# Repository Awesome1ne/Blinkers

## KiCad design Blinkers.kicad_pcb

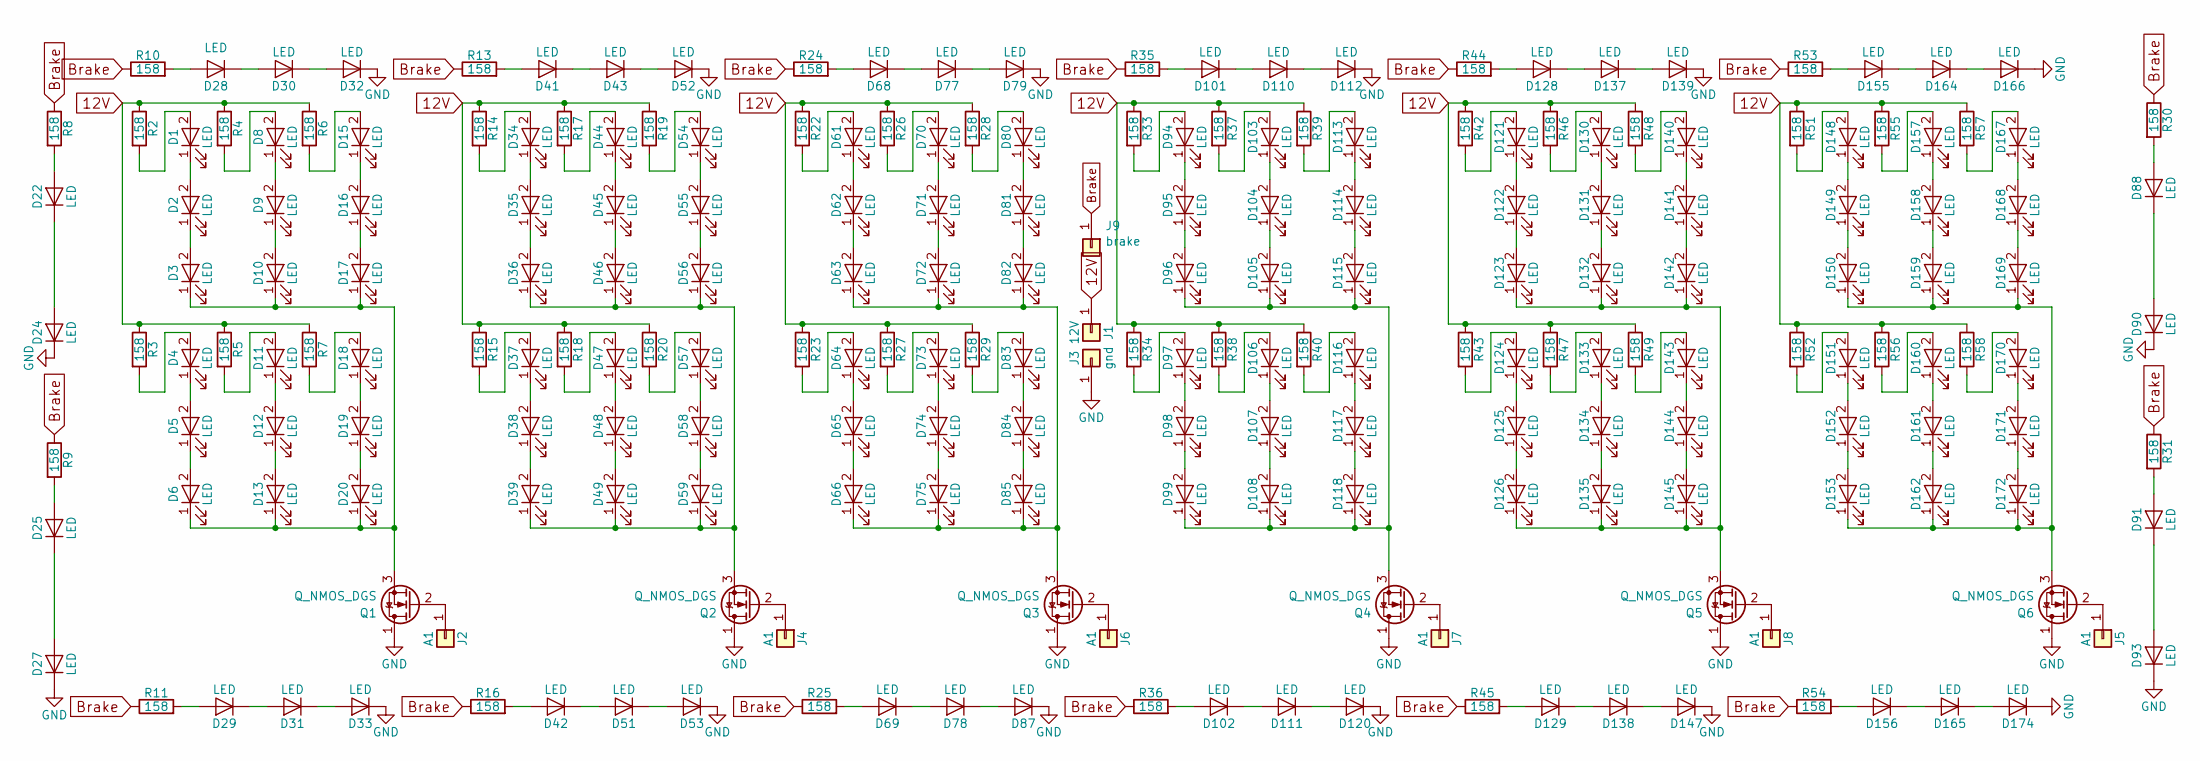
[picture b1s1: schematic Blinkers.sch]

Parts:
D1, D2, D3, D4, D5, D6, D8, D9, D10, D11, D12, D13, D15, D16, D17, D18, D19, D20, D22, D24, D25, D27, D28, D29, D30, D31, D32, D33, D34, D35, D36, D37, D38, D39, D41, D42, D43, D44, D45, D46, D47, D48, D49, D51, D52, D53, D54, D55, D56, D57, D58, D59, D61, D62, D63, D64, D65, D66, D68, D69, D70, D71, D72, D73, D74, D75, D77, D78, D79, D80, D81, D82, D83, D84, D85, D87, D88, D90, D91, D93, D94, D95, D96, D97, D98, D99, D101, D102, D103, D104, D105, D106, D107, D108, D110, D111, D112, D113, D114, D115, D116, D117, D118, D120, D121, D122, D123, D124, D125, D126, D128, D129, D130, D131, D132, D133, D134, D135, D137, D138, D139, D140, D141, D142, D143, D144, D145, D147, D148, D149, D150, D151, D152, D153, D155, D156, D157, D158, D159, D160, D161, D162, D164, D165, D166, D167, D168, D169, D170, D171, D172, D174: LED; D_2835_FLIPPED
J1: 12V; Socket_Strip_Straight_1x01_Pitch2.54mm
J2, J4, J5, J6, J7, J8: A1; Socket_Strip_Straight_1x01_Pitch2.54mm
J3: gnd; Socket_Strip_Straight_1x01_Pitch2.54mm
J9: brake; Socket_Strip_Straight_1x01_Pitch2.54mm
Q1, Q2, Q3, Q4, Q5, Q6: Q_NMOS_DGS; CUSTOM_Socket_Strip_Straight_1x03_Pitch0.09in
R2, R3, R4, R5, R6, R7, R8, R9, R10, R11, R13, R14, R15, R16, R17, R18, R19, R20, R22, R23, R24, R25, R26, R27, R28, R29, R30, R31, R33, R34, R35, R36, R37, R38, R39, R40, R42, R43, R44, R45, R46, R47, R48, R49, R51, R52, R53, R54, R55, R56, R57, R58: 158; Altered_R_1210_3225Metric

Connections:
12V: J1.1, R2.1, R3.1, R4.1, R5.1, R6.1, R7.1, R14.1, R15.1, R17.1, R18.1, R19.1, R20.1, R22.1, R23.1, R26.1, R27.1, R28.1, R29.1, R33.1, R34.1, R37.1, R38.1, R39.1, R40.1, R42.1, R43.1, R46.1, R47.1, R48.1, R49.1, R51.1, R52.1, R55.1, R56.1, R57.1, R58.1
Brake: J9.1, R8.1, R9.1, R10.1, R11.1, R13.1, R16.1, R24.1, R25.1, R30.1, R31.1, R35.1, R36.1, R44.1, R45.1, R53.1, R54.1
GND: D24.1 (K), D27.1 (K), D32.1 (K), D33.1 (K), D52.1 (K), D53.1 (K), D79.1 (K), D87.1 (K), D90.1 (K), D93.1 (K), D112.1 (K), D120.1 (K), D139.1 (K), D147.1 (K), D166.1 (K), D174.1 (K), J3.1, Q1.1 (D), Q2.1 (D), Q3.1 (D), Q4.1 (D), Q5.1 (D), Q6.1 (D)
unnamed: D1.1 (K), D2.2 (A)
unnamed: D1.2 (A), R2.2
unnamed: D2.1 (K), D3.2 (A)
unnamed: D4.1 (K), D5.2 (A)
unnamed: D4.2 (A), R3.2
unnamed: D5.1 (K), D6.2 (A)
unnamed: D8.1 (K), D9.2 (A)
unnamed: D8.2 (A), R4.2
unnamed: D3.1 (K), D6.1 (K), D10.1 (K), D13.1 (K), D17.1 (K), D20.1 (K), Q1.3 (S)
unnamed: D9.1 (K), D10.2 (A)
unnamed: D11.1 (K), D12.2 (A)
unnamed: D11.2 (A), R5.2
unnamed: D12.1 (K), D13.2 (A)
unnamed: D15.1 (K), D16.2 (A)
unnamed: D15.2 (A), R6.2
unnamed: D16.1 (K), D17.2 (A)
unnamed: D18.1 (K), D19.2 (A)
unnamed: D18.2 (A), R7.2
unnamed: D19.1 (K), D20.2 (A)
unnamed: D22.1 (K), D24.2 (A)
unnamed: D22.2 (A), R8.2
unnamed: D25.1 (K), D27.2 (A)
unnamed: D25.2 (A), R9.2
unnamed: D28.1 (K), D30.2 (A)
unnamed: D28.2 (A), R10.2
unnamed: D29.1 (K), D31.2 (A)
unnamed: D29.2 (A), R11.2
unnamed: D30.1 (K), D32.2 (A)
unnamed: D31.1 (K), D33.2 (A)
unnamed: D34.1 (K), D35.2 (A)
unnamed: D34.2 (A), R14.2
unnamed: D35.1 (K), D36.2 (A)
unnamed: D36.1 (K), D39.1 (K), D46.1 (K), D49.1 (K), D56.1 (K), D59.1 (K), Q2.3 (S)
unnamed: D37.1 (K), D38.2 (A)
unnamed: D37.2 (A), R15.2
unnamed: D38.1 (K), D39.2 (A)
unnamed: D41.1 (K), D43.2 (A)
unnamed: D41.2 (A), R13.2
unnamed: D42.1 (K), D51.2 (A)
unnamed: D42.2 (A), R16.2
unnamed: D43.1 (K), D52.2 (A)
unnamed: D44.1 (K), D45.2 (A)
unnamed: D44.2 (A), R17.2
unnamed: D45.1 (K), D46.2 (A)
unnamed: D47.1 (K), D48.2 (A)
unnamed: D47.2 (A), R18.2
unnamed: D48.1 (K), D49.2 (A)
unnamed: D51.1 (K), D53.2 (A)
unnamed: D54.1 (K), D55.2 (A)
unnamed: D54.2 (A), R19.2
unnamed: D55.1 (K), D56.2 (A)
unnamed: D57.1 (K), D58.2 (A)
unnamed: D57.2 (A), R20.2
unnamed: D58.1 (K), D59.2 (A)
unnamed: D61.1 (K), D62.2 (A)
unnamed: D61.2 (A), R22.2
unnamed: D62.1 (K), D63.2 (A)
unnamed: D63.1 (K), D66.1 (K), D72.1 (K), D75.1 (K), D82.1 (K), D85.1 (K), Q3.3 (S)
unnamed: D64.1 (K), D65.2 (A)
unnamed: D64.2 (A), R23.2
unnamed: D65.1 (K), D66.2 (A)
unnamed: D68.1 (K), D77.2 (A)
unnamed: D68.2 (A), R24.2
unnamed: D69.1 (K), D78.2 (A)
unnamed: D69.2 (A), R25.2
unnamed: D70.1 (K), D71.2 (A)
unnamed: D70.2 (A), R26.2
unnamed: D71.1 (K), D72.2 (A)
unnamed: D73.1 (K), D74.2 (A)
unnamed: D73.2 (A), R27.2
unnamed: D74.1 (K), D75.2 (A)
unnamed: D77.1 (K), D79.2 (A)
unnamed: D78.1 (K), D87.2 (A)
unnamed: D80.1 (K), D81.2 (A)
unnamed: D80.2 (A), R28.2
unnamed: D81.1 (K), D82.2 (A)
unnamed: D83.1 (K), D84.2 (A)
unnamed: D83.2 (A), R29.2
unnamed: D84.1 (K), D85.2 (A)
unnamed: D88.1 (K), D90.2 (A)
unnamed: D88.2 (A), R30.2
unnamed: D91.1 (K), D93.2 (A)
unnamed: D91.2 (A), R31.2
unnamed: D94.1 (K), D95.2 (A)
unnamed: D94.2 (A), R33.2
unnamed: D95.1 (K), D96.2 (A)
unnamed: D97.1 (K), D98.2 (A)
unnamed: D97.2 (A), R34.2
unnamed: D98.1 (K), D99.2 (A)
unnamed: D101.1 (K), D110.2 (A)
unnamed: D101.2 (A), R35.2
unnamed: D102.1 (K), D111.2 (A)
unnamed: D102.2 (A), R36.2
unnamed: D103.1 (K), D104.2 (A)
unnamed: D103.2 (A), R37.2
unnamed: D104.1 (K), D105.2 (A)
unnamed: D96.1 (K), D99.1 (K), D105.1 (K), D108.1 (K), D115.1 (K), D118.1 (K), Q4.3 (S)
unnamed: D106.1 (K), D107.2 (A)
unnamed: D106.2 (A), R38.2
unnamed: D107.1 (K), D108.2 (A)
unnamed: D110.1 (K), D112.2 (A)
unnamed: D111.1 (K), D120.2 (A)
unnamed: D113.1 (K), D114.2 (A)
unnamed: D113.2 (A), R39.2
unnamed: D114.1 (K), D115.2 (A)
unnamed: D116.1 (K), D117.2 (A)
unnamed: D116.2 (A), R40.2
unnamed: D117.1 (K), D118.2 (A)
unnamed: D121.1 (K), D122.2 (A)
unnamed: D121.2 (A), R42.2
unnamed: D122.1 (K), D123.2 (A)
unnamed: D123.1 (K), D126.1 (K), D132.1 (K), D135.1 (K), D142.1 (K), D145.1 (K), Q5.3 (S)
unnamed: D124.1 (K), D125.2 (A)
unnamed: D124.2 (A), R43.2
unnamed: D125.1 (K), D126.2 (A)
unnamed: D128.1 (K), D137.2 (A)
unnamed: D128.2 (A), R44.2
unnamed: D129.1 (K), D138.2 (A)
unnamed: D129.2 (A), R45.2
unnamed: D130.1 (K), D131.2 (A)
unnamed: D130.2 (A), R46.2
unnamed: D131.1 (K), D132.2 (A)
unnamed: D133.1 (K), D134.2 (A)
unnamed: D133.2 (A), R47.2
unnamed: D134.1 (K), D135.2 (A)
unnamed: D137.1 (K), D139.2 (A)
unnamed: D138.1 (K), D147.2 (A)
unnamed: D140.1 (K), D141.2 (A)
unnamed: D140.2 (A), R48.2
unnamed: D141.1 (K), D142.2 (A)
unnamed: D143.1 (K), D144.2 (A)
unnamed: D143.2 (A), R49.2
unnamed: D144.1 (K), D145.2 (A)
unnamed: D148.1 (K), D149.2 (A)
unnamed: D148.2 (A), R51.2
unnamed: D149.1 (K), D150.2 (A)
unnamed: D150.1 (K), D153.1 (K), D159.1 (K), D162.1 (K), D169.1 (K), D172.1 (K), Q6.3 (S)
unnamed: D151.1 (K), D152.2 (A)
unnamed: D151.2 (A), R52.2
unnamed: D152.1 (K), D153.2 (A)
unnamed: D155.1 (K), D164.2 (A)
unnamed: D155.2 (A), R53.2
unnamed: D156.1 (K), D165.2 (A)
unnamed: D156.2 (A), R54.2
unnamed: D157.1 (K), D158.2 (A)
unnamed: D157.2 (A), R55.2
unnamed: D158.1 (K), D159.2 (A)
unnamed: D160.1 (K), D161.2 (A)
unnamed: D160.2 (A), R56.2
unnamed: D161.1 (K), D162.2 (A)
unnamed: D164.1 (K), D166.2 (A)
unnamed: D165.1 (K), D174.2 (A)
unnamed: D167.1 (K), D168.2 (A)
unnamed: D167.2 (A), R57.2
unnamed: D168.1 (K), D169.2 (A)
unnamed: D170.1 (K), D171.2 (A)
unnamed: D170.2 (A), R58.2
unnamed: D171.1 (K), D172.2 (A)
unnamed: J2.1, Q1.2 (G)
unnamed: J4.1, Q2.2 (G)
unnamed: J5.1, Q6.2 (G)
unnamed: J6.1, Q3.2 (G)
unnamed: J7.1, Q4.2 (G)
unnamed: J8.1, Q5.2 (G)

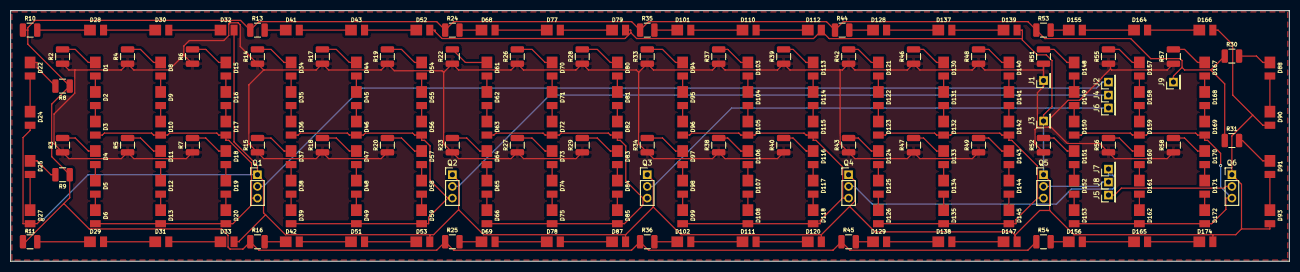
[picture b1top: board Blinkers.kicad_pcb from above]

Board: 2 copper layers, 250.0 x 49.0 mm, 219 parts (0 on the bottom side), 167 nets.

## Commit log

2019-07-05 Re-upload for next stage of changes.
2019-07-05 Re-init
2019-07-09 Modified D_2835 to make it work with specifications for LEDs. Moved VDD and GND pins to appropriate locations near center of board.
2019-07-12 Changed positioning of LED grid with Array tool.
2019-07-12 Aligned right side of outer ring.
2019-07-15 Final basic edit. Ready to branch into product-specific layout.
2019-07-18 Separated VCC and GND
2019-07-18 Changed footprint designators.
    The footprint designators had been all changed to "D1" after using the array tool. In the future we'll need to use a script unless the array tool is fixed.
2019-07-18 Final Revision of Base-Level Board
    Ready to create other version from this base level.
2019-07-18 Edge-cuts have been set to the Nova layout.
2019-07-19 Final board layout, without bottom row of internal LEDs and no separate inputs for outer ring.
    Last upload didn't seem to work with the traces. This one includes the traces.
2019-07-20 Brake connections made in Eeschema.
    "Brake" labels have been assigned to each of the outer LED strips, and a "Brake" input has been made in the center of the layout.
2019-07-24 Main array x-axis positions and top row x-axis positions close to finished, WIP.
2019-07-24 Bottom and right columns aligned.
2019-07-30 Columns and rows aligned. Outer ring aligned. Component designators assigned. VCC and GND positioned. Need to add remaining resistors and position transistors and their inputs.
2019-07-31 Layout complete, ready for tracerouting.
2019-07-31 Nova Board v1 complete!
2019-07-31 Moved VCC and GND inputs.
2019-07-31 Fine-tuning WIP, rotating LEDs for closer connectons and moved VCC and GND.
2019-08-01 Rotation of LEDs complete.
    This should be the final Nova_Layout
2019-08-05 Made changes to Nova_Layout.zip for uploading to JLCPCB for manufacturing.
2019-08-29 Nova_Layout_1-1
    Fixed LED footprint, small pad is GND, large pad is positive. This is opposite of the data sheet.
    Adjusted position of some components for better fit (and fixed R48 and R49)
    Switched the input pins for the transistors to fit a 3x1 set of pins with 2.54mm pitch.
    Changed inner resistor and outer resistor footprints to match original outer footprints.
    Checked all reference numbers to make sure they were the correct size and will be readable when soldering.
2020-01-05 Added power and ground planes
